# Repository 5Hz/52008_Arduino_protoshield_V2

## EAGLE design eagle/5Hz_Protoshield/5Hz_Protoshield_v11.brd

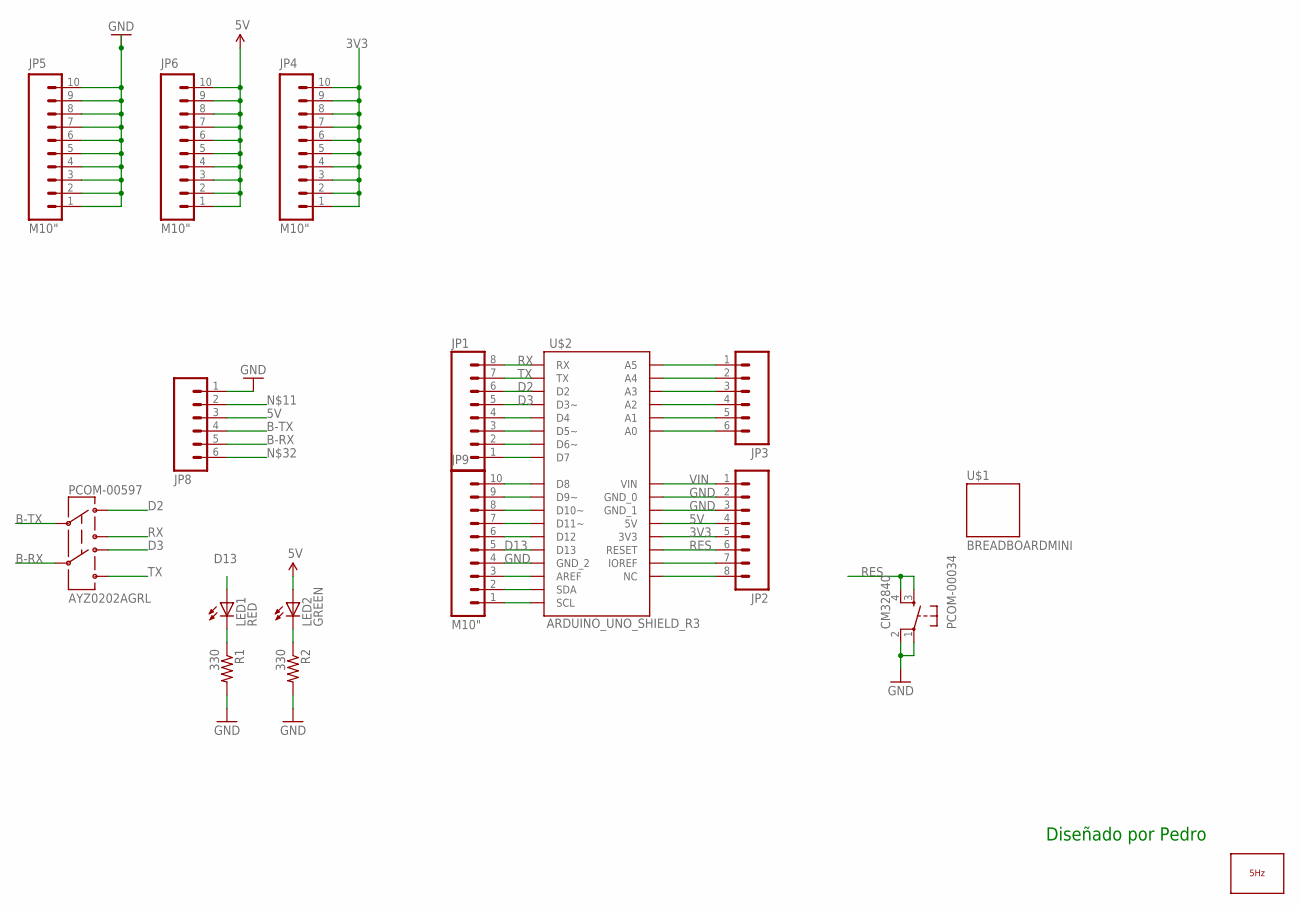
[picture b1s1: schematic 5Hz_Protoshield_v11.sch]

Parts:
JP1, JP2: M081X08; 1X08
JP3, JP8: M06SIP; 1X06
JP4, JP5, JP6, JP9: M10"; 1X10
LED1: RED; LED-0603
LED2: GREEN; LED-0603
LOGO1: LOGO_5HZ_H_10MM; 5HZ_LOGO_H_10MM
PCOM-00034: CM32840; TACTILE_SWITCH_SMD
PCOM-00597: AYZ0202AGRL; AYZ0202
R1, R2: 330; 0603-RES
U$1: BREADBOARDMINI; BREADBOARD-MINI
U$2: ARDUINO_UNO_SHIELD_R3; UNO_R3_SHIELD_NO_SILK

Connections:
3V3: JP2.5, JP4.1, JP4.2, JP4.3, JP4.4, JP4.5, JP4.6, JP4.7, JP4.8, JP4.9, JP4.10, U$2.3.3V (3V3)
5V: JP2.4, JP6.1, JP6.2, JP6.3, JP6.4, JP6.5, JP6.6, JP6.7, JP6.8, JP6.9, JP6.10, JP8.3, LED2.A, U$2.5V
B-RX: JP8.5, PCOM-00597.5
B-TX: JP8.4, PCOM-00597.2
D2: JP1.6, PCOM-00597.1, U$2.D2
D3: JP1.5, PCOM-00597.4, U$2.D3 (D3~)
D13: JP9.5, LED1.A, U$2.D13
GND: JP2.2, JP2.3, JP5.1, JP5.2, JP5.3, JP5.4, JP5.5, JP5.6, JP5.7, JP5.8, JP5.9, JP5.10, JP8.1, JP9.4, PCOM-00034.1, PCOM-00034.2, R1.2, R2.2, U$2.GND_0, U$2.GND_1, U$2.GND_2
unnamed: JP1.1, U$2.D7
unnamed: JP1.2, U$2.D6 (D6~)
unnamed: JP1.3, U$2.D5 (D5~)
unnamed: JP1.4, U$2.D4
unnamed: JP9.3, U$2.AREF
unnamed: LED1.C, R1.1
unnamed: JP9.6, U$2.D12
unnamed: JP9.7, U$2.D11 (D11~)
unnamed: JP9.8, U$2.D10 (D10~)
unnamed: JP9.9, U$2.D9 (D9~)
unnamed: JP9.10, U$2.D8
unnamed: JP3.1, U$2.A5
unnamed: JP3.2, U$2.A4
unnamed: JP3.3, U$2.A3
unnamed: JP3.4, U$2.A2
unnamed: JP3.5, U$2.A1
unnamed: JP3.6, U$2.A0
unnamed: JP9.2, U$2.SDA
unnamed: LED2.C, R2.1
unnamed: JP9.1, U$2.SCL
unnamed: JP2.7, U$2.IOREF
unnamed: JP2.8, U$2.NC
RES: JP2.6, PCOM-00034.3, PCOM-00034.4, U$2.RES (RESET)
RX: JP1.8, PCOM-00597.3, U$2.RX
TX: JP1.7, PCOM-00597.6, U$2.TX
VIN: JP2.1, U$2.VIN

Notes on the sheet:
Diseñado por Pedro

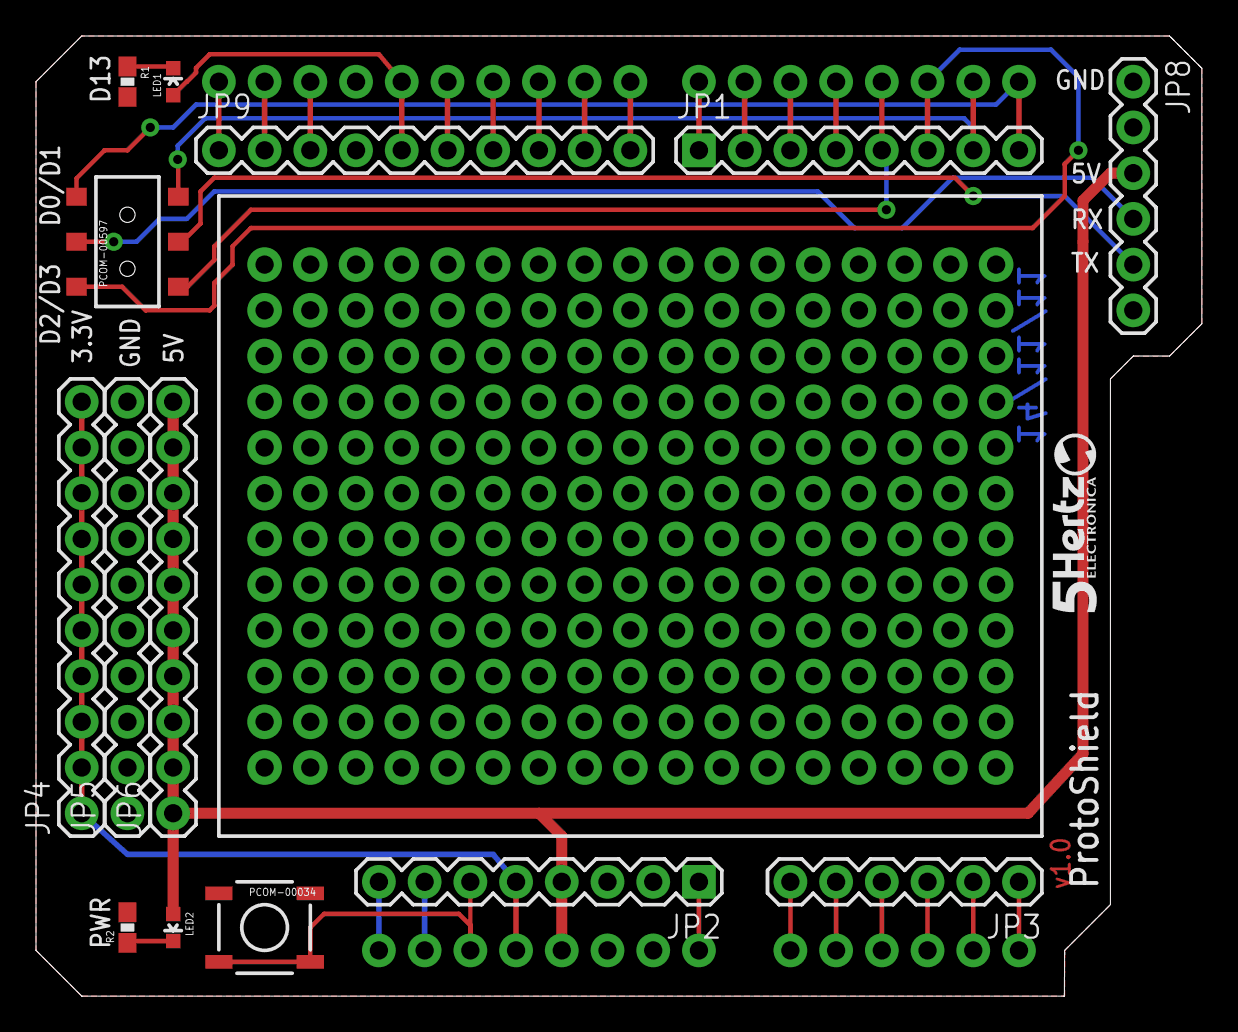
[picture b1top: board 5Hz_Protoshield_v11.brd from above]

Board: 2 copper layers, 64.8 x 53.3 mm, 17 parts (0 on the bottom side), 34 nets.

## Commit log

2014-01-14 creación
